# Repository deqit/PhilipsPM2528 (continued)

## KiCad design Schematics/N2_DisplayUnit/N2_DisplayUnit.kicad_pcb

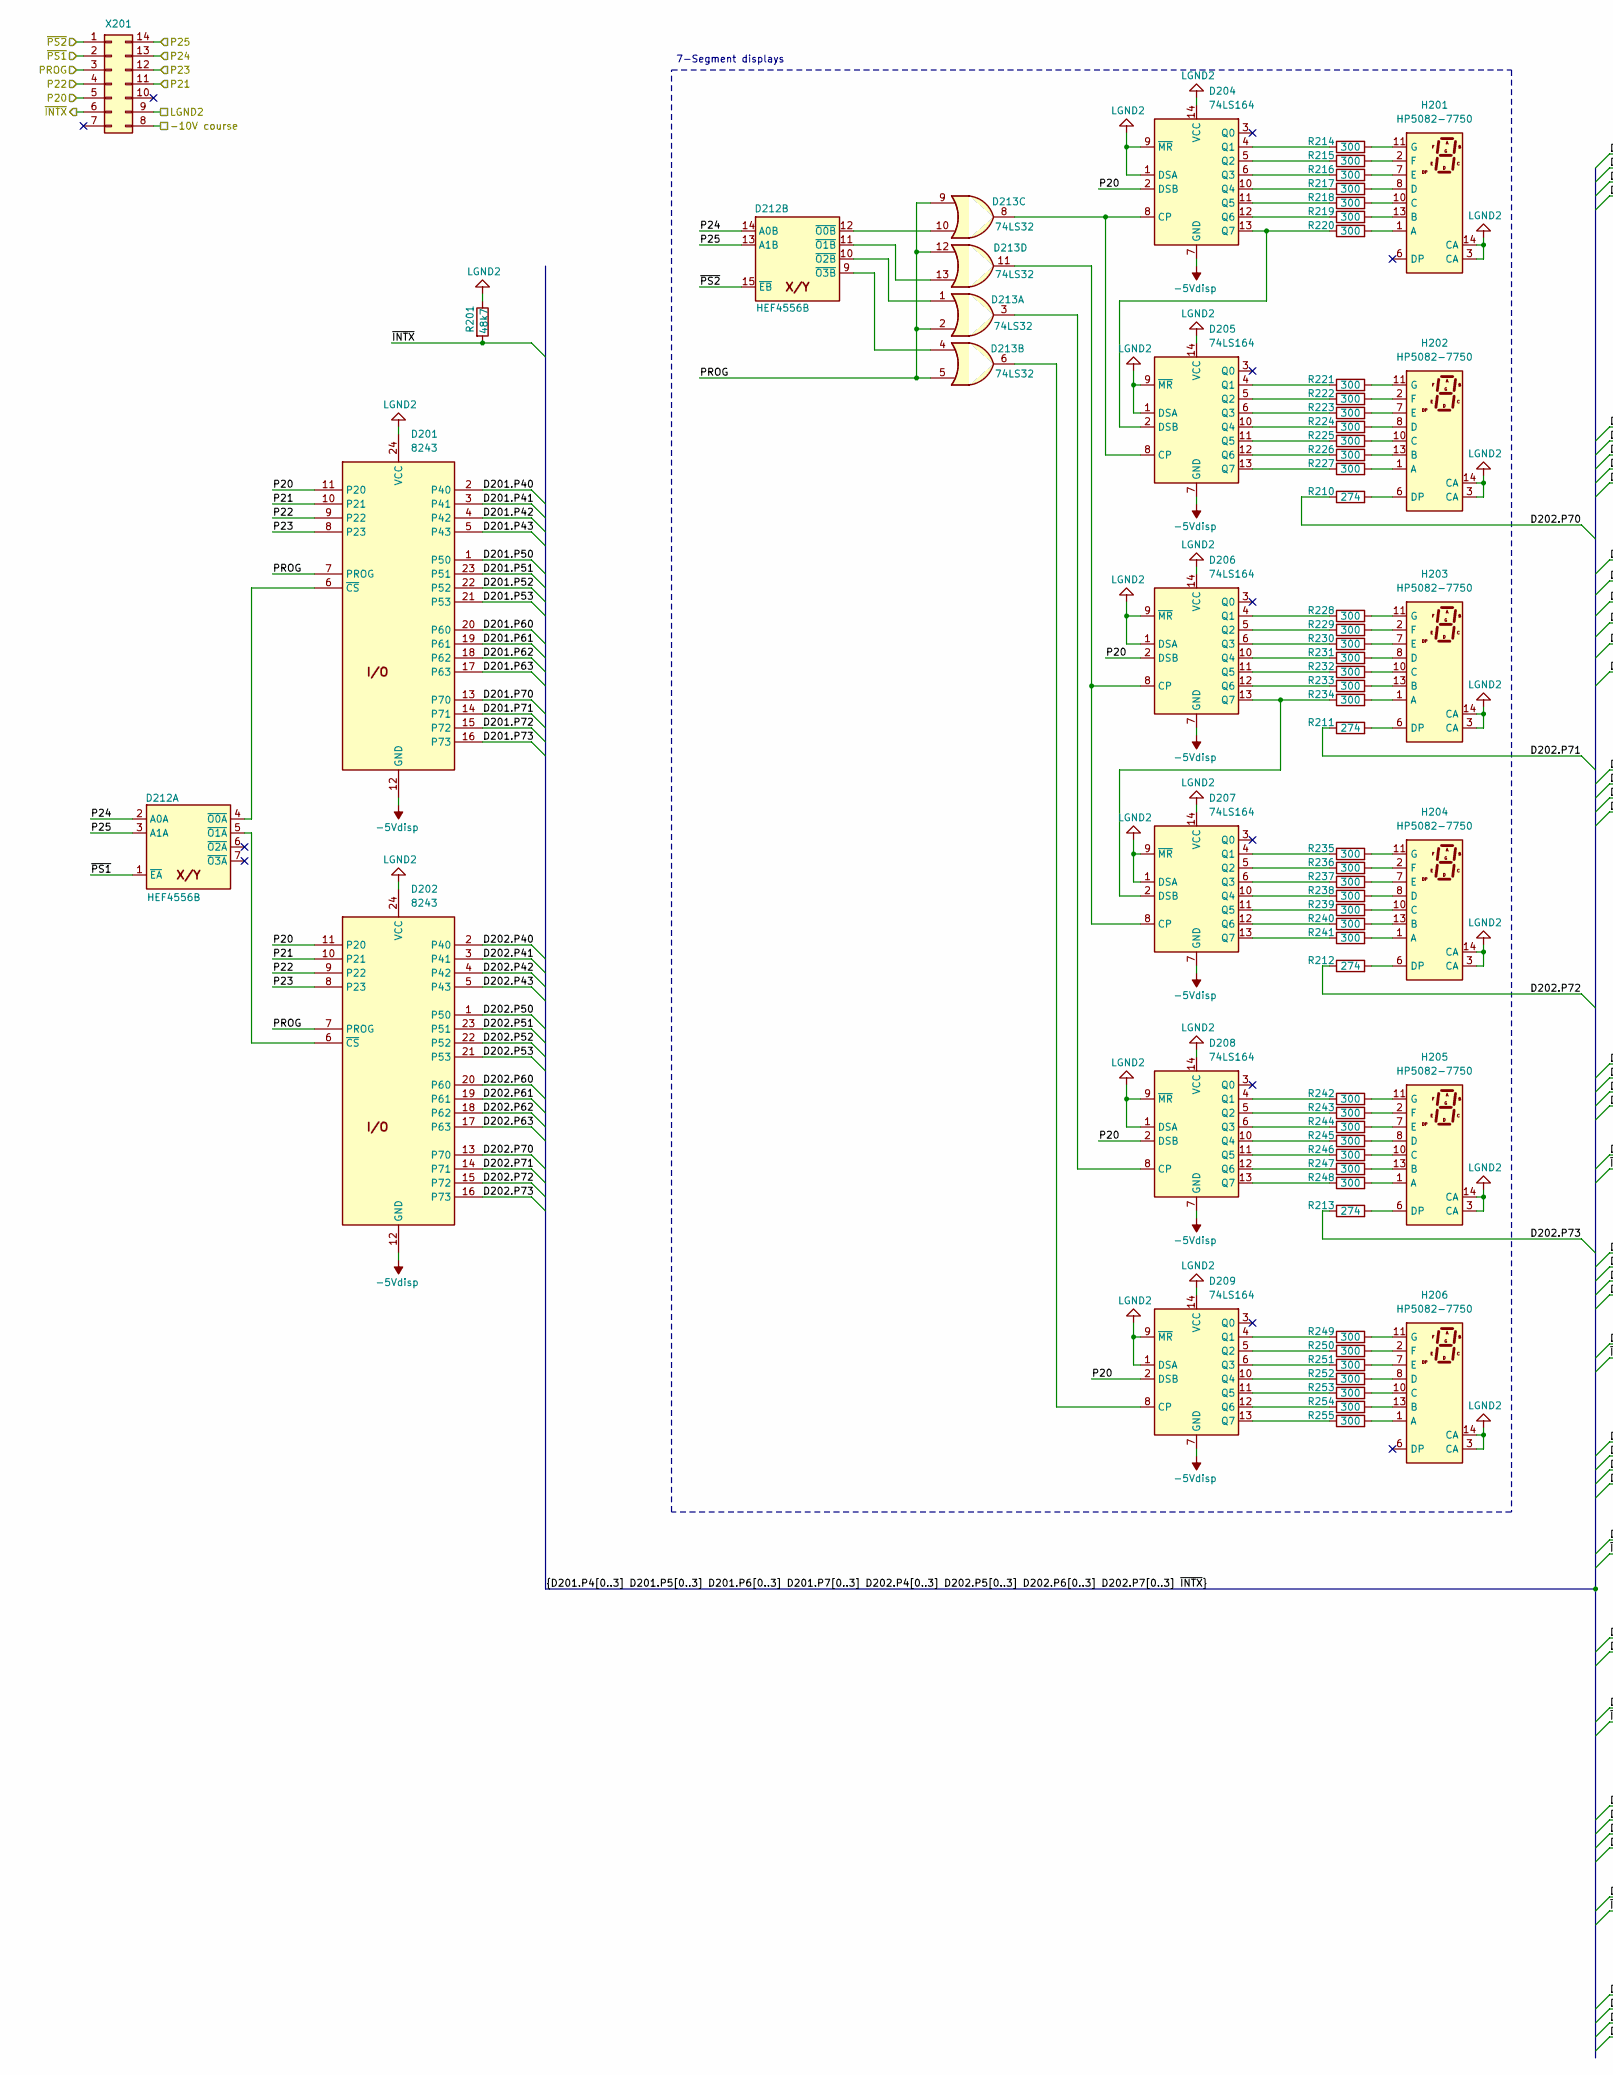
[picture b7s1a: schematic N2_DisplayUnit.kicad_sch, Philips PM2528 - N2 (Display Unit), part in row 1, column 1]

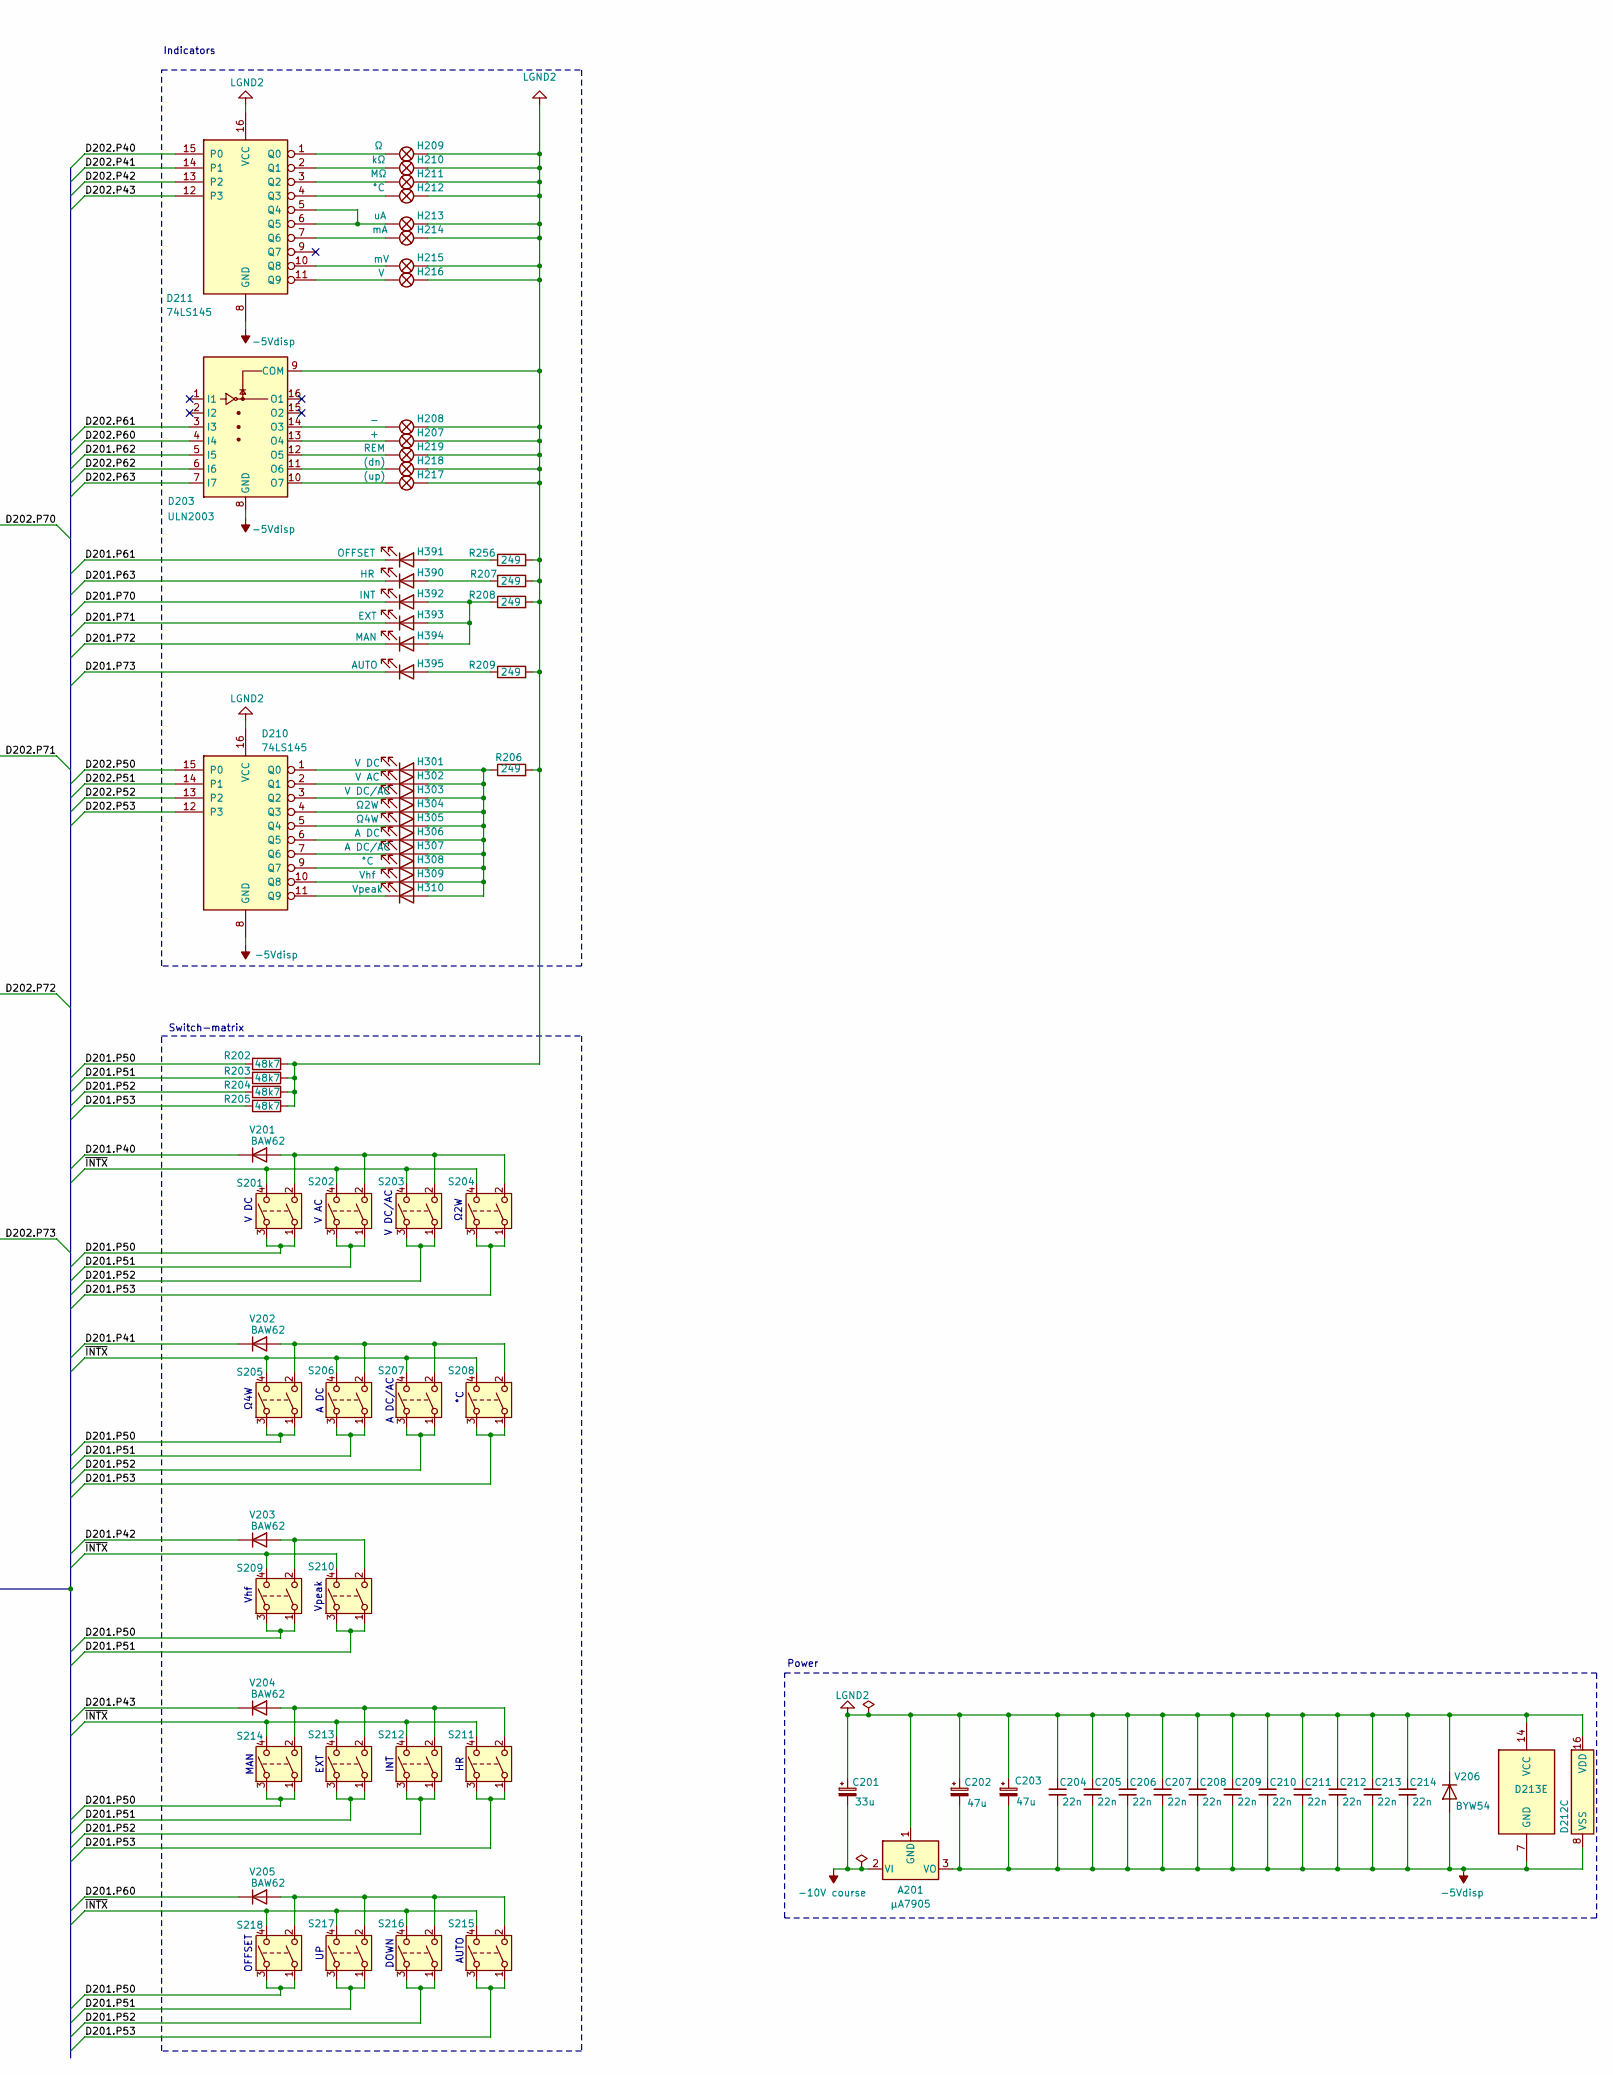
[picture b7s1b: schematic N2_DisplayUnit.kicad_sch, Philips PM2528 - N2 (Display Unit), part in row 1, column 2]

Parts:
A201: µA7905; TO-220-3_Vertical
C201: 33u; CP_Axial_L10.0mm_D4.5mm_P15.00mm_Horizontal
C202, C203: 47u; CP_Axial_L10.0mm_D6.0mm_P15.00mm_Horizontal
C204, C205, C206, C207, C208, C209, C210, C211, C212, C213, C214: 22n; C_Disc_D5.0mm_W2.5mm_P5.00mm
D201, D202: 8243; DIP-24_W15.24mm
D203: ULN2003; DIP-16_W7.62mm
D204, D205, D206, D207, D208, D209: 74LS164; DIP-14_W7.62mm
D210, D211: 74LS145; DIP-16_W7.62mm
D212: HEF4556B; DIP-16_W7.62mm
D213: 74LS32; DIP-14_W7.62mm
H201, H202, H203, H204, H205, H206: HP5082-7750; MAN3820A
H207: +; LED_D3.0mm
H208: -; LED_D3.0mm
H209: Ω; LED_D3.0mm
H210: kΩ; LED_D3.0mm
H211: MΩ; LED_D3.0mm
H212, H308: °C; LED_D3.0mm
H213: uA; LED_D3.0mm
H214: mA; LED_D3.0mm
H215: mV; LED_D3.0mm
H216: V; LED_D3.0mm
H217: (up); LED_D3.0mm
H218: (dn); LED_D3.0mm
H219: REM; LED_D3.0mm
H301: V DC; LED_D3.0mm
H302: V AC; LED_D3.0mm
H303: V DC/AC; LED_D3.0mm
H304: Ω2W; LED_D3.0mm
H305: Ω4W; LED_D3.0mm
H306: A DC; LED_D3.0mm
H307: A DC/AC; LED_D3.0mm
H309: Vhf; LED_D3.0mm
H310: Vpeak; LED_D3.0mm
H390: HR; LED_D3.0mm
H391: OFFSET; LED_D3.0mm
H392: INT; LED_D3.0mm
H393: EXT; LED_D3.0mm
H394: MAN; LED_D3.0mm
H395: AUTO; LED_D3.0mm
R201, R202, R203, R204, R205: 48k7; R_Axial_DIN0207_L6.3mm_D2.5mm_P10.16mm_Horizontal
R206, R207, R208, R209, R256: 249; R_Axial_DIN0207_L6.3mm_D2.5mm_P10.16mm_Horizontal
R210, R211, R212, R213: 274; R_Axial_DIN0207_L6.3mm_D2.5mm_P10.16mm_Horizontal
R214, R215, R216, R217, R218, R219, R220, R221, R222, R223, R224, R225, R226, R227, R228, R229, R230, R231, R232, R233, R234, R235, R236, R237, R238, R239, R240, R241, R242, R243, R244, R245, R246, R247, R248, R249, R250, R251, R252, R253, R254, R255: 300; R_Axial_DIN0207_L6.3mm_D2.5mm_P2.54mm_Vertical
S201, S202, S203, S204, S205, S206, S207, S208, S209, S210, S211, S212, S213, S214, S215, S216, S217, S218: SW_DPST; SW_Push_2P1T_Toggle_CK_PVA1xxH1xxxxxxV2
V201, V202, V203, V204, V205: BAW62; D_DO-35_SOD27_P10.16mm_Horizontal
V206: BYW54; D_DO-35_SOD27_P10.16mm_Horizontal
X201: Conn_02x07_Counter_Clockwise; DIP-14_W10.16mm

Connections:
-5Vdisp: A201.3 (VO), C202.2, C203.2, C204.2, C205.2, C206.2, C207.2, C208.2, C209.2, C210.2, C211.2, C212.2, C213.2, C214.2, D201.12 (GND), D202.12 (GND), D203.8 (GND), D204.7 (GND), D205.7 (GND), D206.7 (GND), D207.7 (GND), D208.7 (GND), D209.7 (GND), D210.8 (GND), D211.8 (GND), D212.8 (VSS), D213.7 (GND), V206.2 (A)
-10V course: A201.2 (VI), C201.2, X201.8
/D201.P40: D201.2 (P40), V201.1 (K)
/D201.P41: D201.3 (P41), V202.1 (K)
/D201.P42: D201.4 (P42), V203.1 (K)
/D201.P43: D201.5 (P43), V204.1 (K)
/D201.P50: D201.1 (P50), R202.2, S201.1, S201.3, S205.1, S205.3, S209.1, S209.3, S214.1, S214.3, S218.1, S218.3
/D201.P51: D201.23 (P51), R203.2, S202.1, S202.3, S206.1, S206.3, S210.1, S210.3, S213.1, S213.3, S217.1, S217.3
/D201.P52: D201.22 (P52), R204.2, S203.1, S203.3, S207.1, S207.3, S212.1, S212.3, S216.1, S216.3
/D201.P53: D201.21 (P53), R205.2, S204.1, S204.3, S208.1, S208.3, S211.1, S211.3, S215.1, S215.3
/D201.P60: D201.20 (P60), V205.1 (K)
/D201.P61: D201.19 (P61), H391.1 (K)
/D201.P62: D201.18 (P62), D203.5 (I5)
/D201.P63: D201.17 (P63), H390.1 (K)
/D201.P70: D201.13 (P70), H392.1 (K)
/D201.P71: D201.14 (P71), H393.1 (K)
/D201.P72: D201.15 (P72), H394.1 (K)
/D201.P73: D201.16 (P73), H395.1 (K)
/D202.P40: D202.2 (P40), D211.15 (P0)
/D202.P41: D202.3 (P41), D211.14 (P1)
/D202.P42: D202.4 (P42), D211.13 (P2)
/D202.P43: D202.5 (P43), D211.12 (P3)
/D202.P50: D202.1 (P50), D210.15 (P0)
/D202.P51: D202.23 (P51), D210.14 (P1)
/D202.P52: D202.22 (P52), D210.13 (P2)
/D202.P53: D202.21 (P53), D210.12 (P3)
/D202.P60: D202.20 (P60), D203.4 (I4)
/D202.P61: D202.19 (P61), D203.3 (I3)
/D202.P62: D202.18 (P62), D203.6 (I6)
/D202.P63: D202.17 (P63), D203.7 (I7)
/D202.P70: D202.13 (P70), R210.1
/D202.P71: D202.14 (P71), R211.1
/D202.P72: D202.15 (P72), R212.1
/D202.P73: D202.16 (P73), R213.1
/LGND2: A201.1 (GND), C201.1, C202.1, C203.1, C204.1, C205.1, C206.1, C207.1, C208.1, C209.1, C210.1, C211.1, C212.1, C213.1, C214.1, D201.24 (VCC), D202.24 (VCC), D203.9 (COM), D204.1 (DSA), D204.9 (~MR), D204.14 (VCC), D205.1 (DSA), D205.9 (~MR), D205.14 (VCC), D206.1 (DSA), D206.9 (~MR), D206.14 (VCC), D207.1 (DSA), D207.9 (~MR), D207.14 (VCC), D208.1 (DSA), D208.9 (~MR), D208.14 (VCC), D209.1 (DSA), D209.9 (~MR), D209.14 (VCC), D210.16 (VCC), D211.16 (VCC), D212.16 (VDD), D213.14 (VCC), H201.3 (CA), H201.14 (CA), H202.3 (CA), H202.14 (CA), H203.3 (CA), H203.14 (CA), H204.3 (CA), H204.14 (CA), H205.3 (CA), H205.14 (CA), H206.3 (CA), H206.14 (CA), H207.2, H208.2, H209.2, H210.2, H211.2, H212.2, H213.2, H214.2, H215.2, H216.2, H217.2, H218.2, H219.2, R201.1, R202.1, R203.1, R204.1, R205.1, R206.2, R207.2, R208.2, R209.2, R256.2, V206.1 (K), X201.9
/P20: D201.11 (P20), D202.11 (P20), D204.2 (DSB), D206.2 (DSB), D208.2 (DSB), D209.2 (DSB), X201.5
/P21: D201.10 (P21), D202.10 (P21), X201.11
/P22: D201.9 (P22), D202.9 (P22), X201.4
/P23: D201.8 (P23), D202.8 (P23), X201.12
/P24: D212.2 (A0A), D212.14 (A0B), X201.13
/P25: D212.3 (A1A), D212.13 (A1B), X201.14
/PROG: D201.7 (PROG), D202.7 (PROG), D213.2, D213.5, D213.9, D213.12, X201.3
/~INTX: R201.2, S201.4, S202.4, S203.4, S204.4, S205.4, S206.4, S207.4, S208.4, S209.4, S210.4, S211.4, S212.4, S213.4, S214.4, S215.4, S216.4, S217.4, S218.4, X201.6
/~PS1: D212.1 (~EA), X201.2
/~PS2: D212.15 (~EB), X201.1
unnamed: D201.6 (~CS), D212.4 (~O0A)
unnamed: D202.6 (~CS), D212.5 (~O1A)
unnamed: D203.14 (O3), H208.1
unnamed: D203.13 (O4), H207.1
unnamed: D203.12 (O5), H219.1
unnamed: D203.11 (O6), H218.1
unnamed: D203.10 (O7), H217.1
unnamed: D204.8 (CP), D205.8 (CP), D213.8
unnamed: D204.4 (Q1), R214.1
unnamed: D204.5 (Q2), R215.1
unnamed: D204.6 (Q3), R216.1
unnamed: D204.10 (Q4), R217.1
unnamed: D204.11 (Q5), R218.1
unnamed: D204.12 (Q6), R219.1
unnamed: D204.13 (Q7), D205.2 (DSB), R220.1
unnamed: D205.4 (Q1), R221.1
unnamed: D205.5 (Q2), R222.1
unnamed: D205.6 (Q3), R223.1
unnamed: D205.10 (Q4), R224.1
unnamed: D205.11 (Q5), R225.1
unnamed: D205.12 (Q6), R226.1
unnamed: D205.13 (Q7), R227.1
unnamed: D206.8 (CP), D207.8 (CP), D213.11
unnamed: D206.4 (Q1), R228.1
unnamed: D206.5 (Q2), R229.1
unnamed: D206.6 (Q3), R230.1
unnamed: D206.10 (Q4), R231.1
unnamed: D206.11 (Q5), R232.1
unnamed: D206.12 (Q6), R233.1
unnamed: D206.13 (Q7), D207.2 (DSB), R234.1
unnamed: D207.4 (Q1), R235.1
unnamed: D207.5 (Q2), R236.1
unnamed: D207.6 (Q3), R237.1
unnamed: D207.10 (Q4), R238.1
unnamed: D207.11 (Q5), R239.1
unnamed: D207.12 (Q6), R240.1
unnamed: D207.13 (Q7), R241.1
unnamed: D208.8 (CP), D213.3
unnamed: D208.4 (Q1), R242.1
unnamed: D208.5 (Q2), R243.1
unnamed: D208.6 (Q3), R244.1
unnamed: D208.10 (Q4), R245.1
unnamed: D208.11 (Q5), R246.1
unnamed: D208.12 (Q6), R247.1
unnamed: D208.13 (Q7), R248.1
unnamed: D209.8 (CP), D213.6
unnamed: D209.4 (Q1), R249.1
unnamed: D209.5 (Q2), R250.1
unnamed: D209.6 (Q3), R251.1
unnamed: D209.10 (Q4), R252.1
unnamed: D209.11 (Q5), R253.1
unnamed: D209.12 (Q6), R254.1
unnamed: D209.13 (Q7), R255.1
unnamed: D210.1 (Q0), H301.1 (K)
unnamed: D210.2 (Q1), H302.1 (K)
unnamed: D210.3 (Q2), H303.1 (K)
unnamed: D210.4 (Q3), H304.1 (K)
unnamed: D210.5 (Q4), H305.1 (K)
unnamed: D210.6 (Q5), H306.1 (K)
unnamed: D210.7 (Q6), H307.1 (K)
unnamed: D210.9 (Q7), H308.1 (K)
unnamed: D210.10 (Q8), H309.1 (K)
unnamed: D210.11 (Q9), H310.1 (K)
unnamed: D211.1 (Q0), H209.1
unnamed: D211.2 (Q1), H210.1
unnamed: D211.3 (Q2), H211.1
unnamed: D211.4 (Q3), H212.1
unnamed: D211.5 (Q4), D211.6 (Q5), H213.1
unnamed: D211.7 (Q6), H214.1
unnamed: D211.10 (Q8), H215.1
unnamed: D211.11 (Q9), H216.1
unnamed: D212.12 (~O0B), D213.10
unnamed: D212.11 (~O1B), D213.13
unnamed: D212.10 (~O2B), D213.1
unnamed: D212.9 (~O3B), D213.4
unnamed: H201.1 (A), R220.2
unnamed: H201.13 (B), R219.2
unnamed: H201.10 (C), R218.2
unnamed: H201.8 (D), R217.2
unnamed: H201.7 (E), R216.2
unnamed: H201.2 (F), R215.2
unnamed: H201.11 (G), R214.2
unnamed: H202.1 (A), R227.2
unnamed: H202.13 (B), R226.2
unnamed: H202.10 (C), R225.2
unnamed: H202.8 (D), R224.2
unnamed: H202.6 (DP), R210.2
unnamed: H202.7 (E), R223.2
unnamed: H202.2 (F), R222.2
unnamed: H202.11 (G), R221.2
unnamed: H203.1 (A), R234.2
unnamed: H203.13 (B), R233.2
unnamed: H203.10 (C), R232.2
unnamed: H203.8 (D), R231.2
unnamed: H203.6 (DP), R211.2
unnamed: H203.7 (E), R230.2
unnamed: H203.2 (F), R229.2
unnamed: H203.11 (G), R228.2
unnamed: H204.1 (A), R241.2
unnamed: H204.13 (B), R240.2
unnamed: H204.10 (C), R239.2
unnamed: H204.8 (D), R238.2
unnamed: H204.6 (DP), R212.2
unnamed: H204.7 (E), R237.2
unnamed: H204.2 (F), R236.2
unnamed: H204.11 (G), R235.2
unnamed: H205.1 (A), R248.2
unnamed: H205.13 (B), R247.2
unnamed: H205.10 (C), R246.2
unnamed: H205.8 (D), R245.2
unnamed: H205.6 (DP), R213.2
unnamed: H205.7 (E), R244.2
unnamed: H205.2 (F), R243.2
unnamed: H205.11 (G), R242.2
unnamed: H206.1 (A), R255.2
unnamed: H206.13 (B), R254.2
unnamed: H206.10 (C), R253.2
unnamed: H206.8 (D), R252.2
unnamed: H206.7 (E), R251.2
unnamed: H206.2 (F), R250.2
unnamed: H206.11 (G), R249.2
unnamed: H301.2 (A), H302.2 (A), H303.2 (A), H304.2 (A), H305.2 (A), H306.2 (A), H307.2 (A), H308.2 (A), H309.2 (A), H310.2 (A), R206.1
unnamed: H390.2 (A), R207.1
unnamed: H391.2 (A), R256.1
unnamed: H392.2 (A), H393.2 (A), H394.2 (A), R208.1
unnamed: H395.2 (A), R209.1
unnamed: S201.2, S202.2, S203.2, S204.2, V201.2 (A)
unnamed: S205.2, S206.2, S207.2, S208.2, V202.2 (A)
unnamed: S209.2, S210.2, V203.2 (A)
unnamed: S211.2, S212.2, S213.2, S214.2, V204.2 (A)
unnamed: S215.2, S216.2, S217.2, S218.2, V205.2 (A)

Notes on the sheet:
Vhf
AUTO
Power
OFFSET
MAN
DOWN
V AC
Indicators
V DC
Switch-matrix
A DC
V DC/AC
Vpeak
EXT
7-Segment displays
Ω4W
Ω2W
A DC/AC
INT

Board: 2 copper layers, 144 parts (0 on the bottom side), 176 nets, no tracks yet.

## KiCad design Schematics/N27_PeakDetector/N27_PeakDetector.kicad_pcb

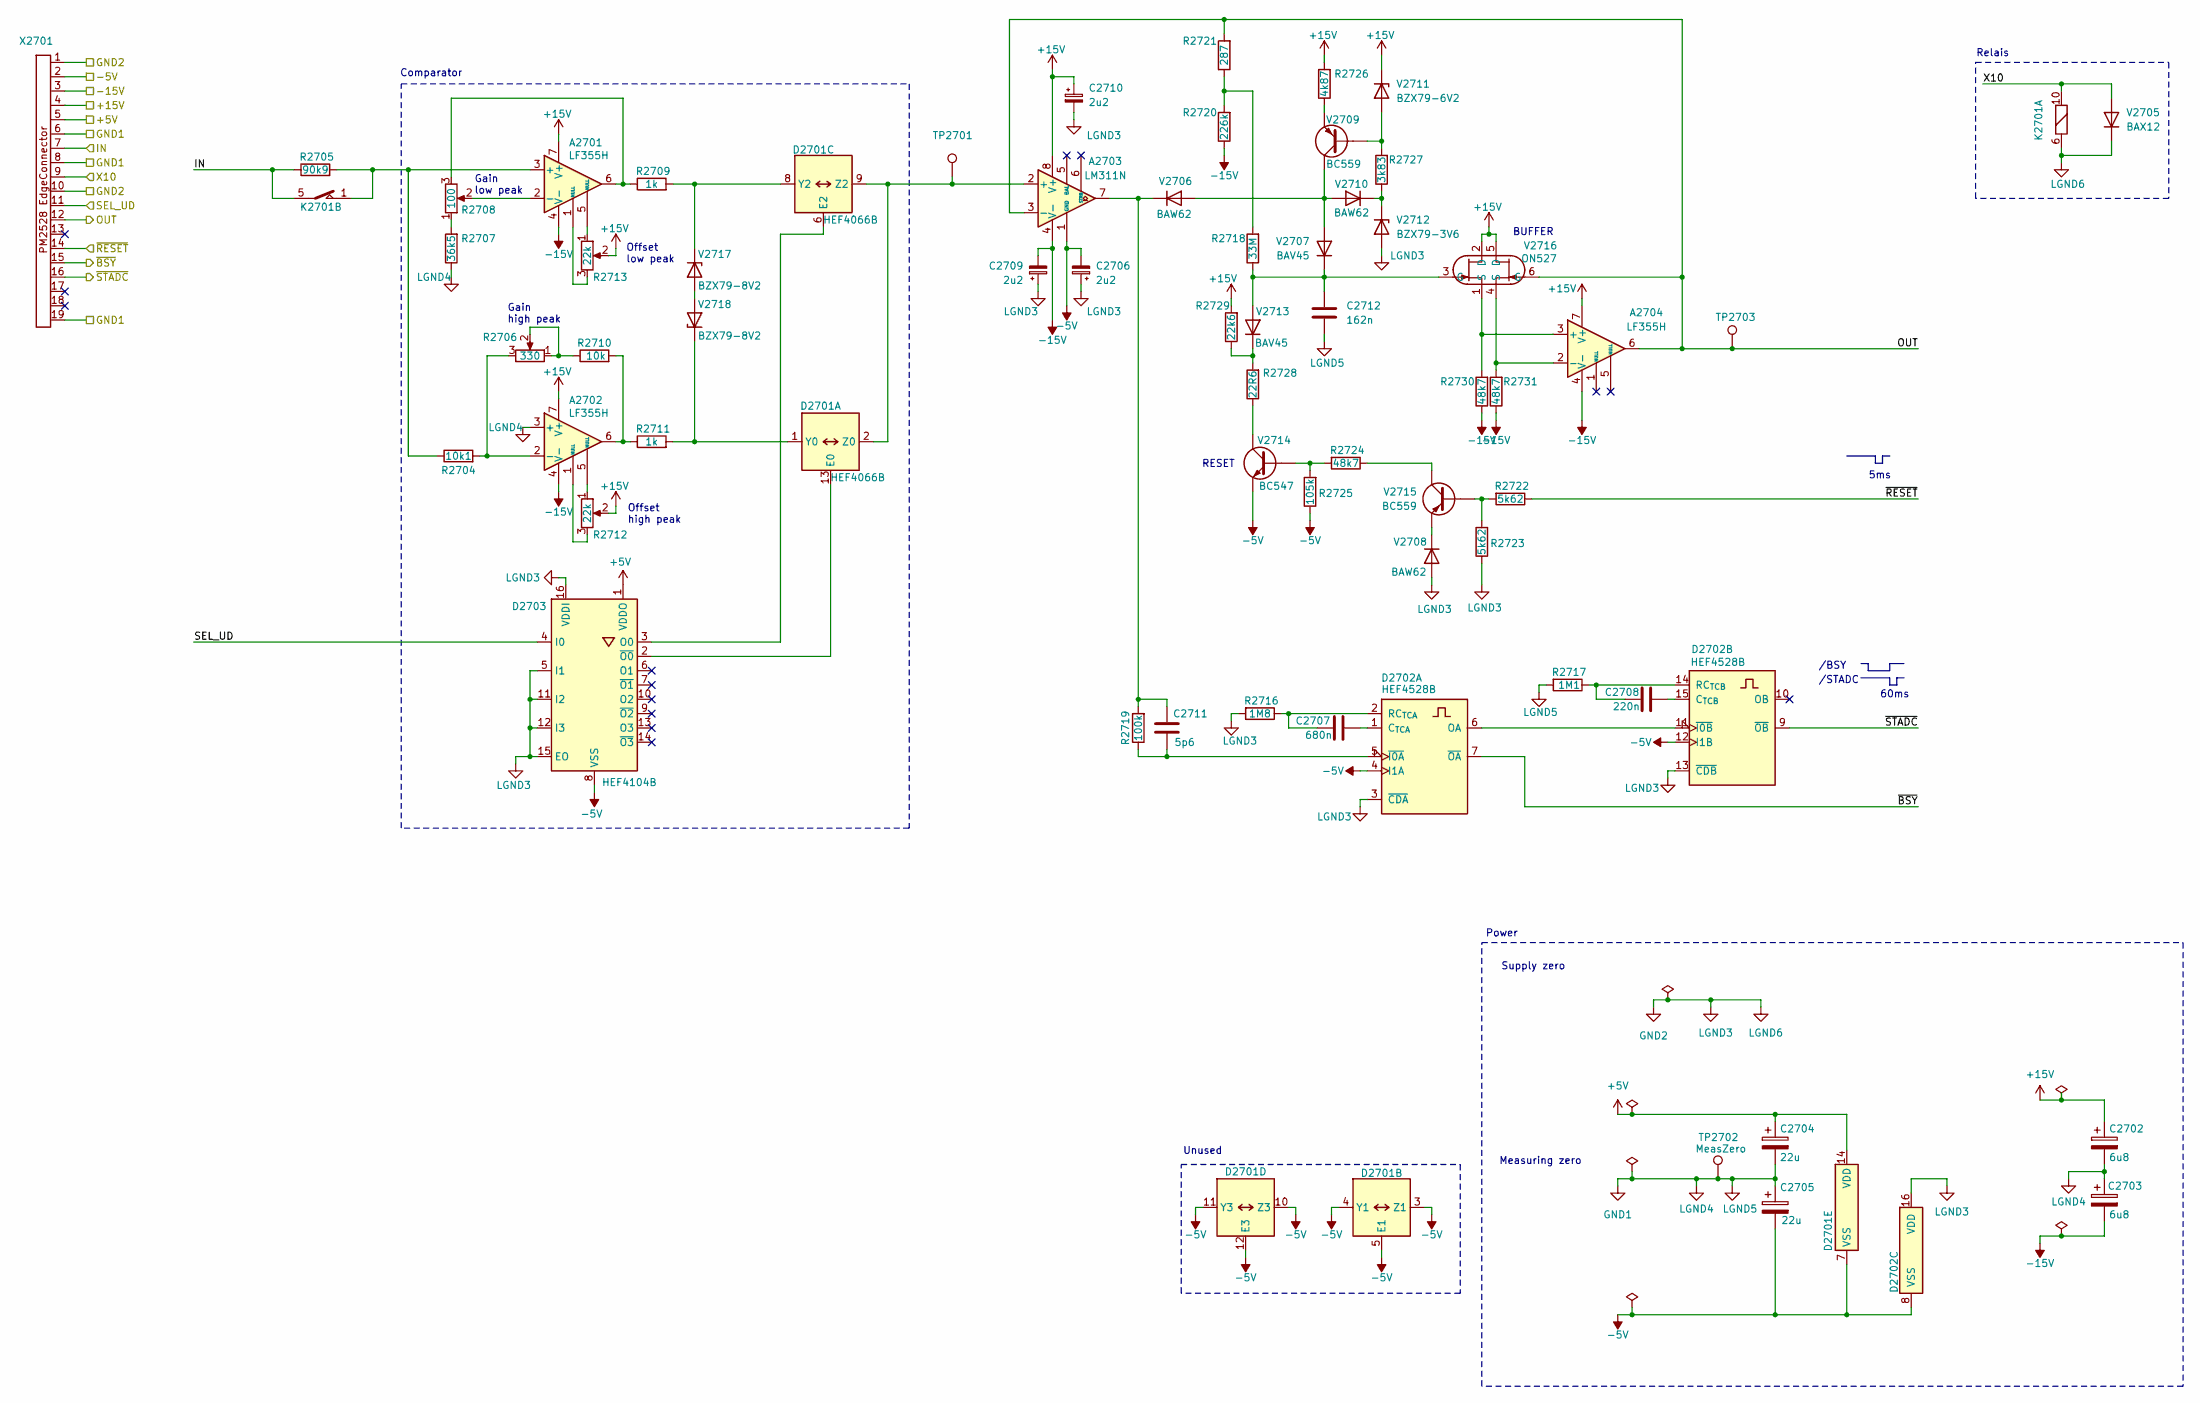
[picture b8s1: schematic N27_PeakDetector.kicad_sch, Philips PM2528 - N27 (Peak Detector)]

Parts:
A2701, A2702, A2704: LF355H; DIP-8_W7.62mm
A2703: LM311N; DIP-8_W7.62mm
C2702, C2703: 6u8; CP_Radial_Tantal_D4.5mm_P5.00mm
C2704, C2705: 22u; CP_Radial_Tantal_D4.5mm_P5.00mm
C2706, C2709, C2710: 2u2; C_Disc_D5.0mm_W2.5mm_P5.00mm
C2707: 680n; C_Rect_L18.0mm_W5.0mm_P15.00mm_FKS3_FKP3
C2708: 220n; C_Rect_L13.0mm_W4.0mm_P10.00mm_FKS3_FKP3_MKS4
C2711: 5p6
C2712: 162n; CP_Axial_L25.0mm_D10.0mm_P30.00mm_Horizontal
D2701: HEF4066B; DIP-14_W7.62mm
D2702: HEF4528B; DIP-16_W7.62mm
D2703: HEF4104B; DIP-16_W7.62mm
K2701: (no value)
R2704: 10k1; R_Axial_DIN0207_L6.3mm_D2.5mm_P10.16mm_Horizontal
R2705: 90k9; R_Axial_DIN0207_L6.3mm_D2.5mm_P10.16mm_Horizontal
R2706: 330; Trimmer vertical
R2707: 36k5; R_Axial_DIN0207_L6.3mm_D2.5mm_P10.16mm_Horizontal
R2708: 100; Trimmer vertical
R2709, R2711: 1k; R_Axial_DIN0207_L6.3mm_D2.5mm_P10.16mm_Horizontal
R2710: 10k; R_Axial_DIN0207_L6.3mm_D2.5mm_P10.16mm_Horizontal
R2712, R2713: 22k; Trimmer vertical
R2716: 1M8; R_Axial_DIN0207_L6.3mm_D2.5mm_P10.16mm_Horizontal
R2717: 1M1; R_Axial_DIN0207_L6.3mm_D2.5mm_P10.16mm_Horizontal
R2718: 33M; R_Axial_DIN0309_L9.0mm_D3.2mm_P15.24mm_Horizontal
R2719: 100k; R_Axial_DIN0207_L6.3mm_D2.5mm_P10.16mm_Horizontal
R2720: 226k; R_Axial_DIN0207_L6.3mm_D2.5mm_P10.16mm_Horizontal
R2721: 287; R_Axial_DIN0207_L6.3mm_D2.5mm_P10.16mm_Horizontal
R2722, R2723: 5k62; R_Axial_DIN0207_L6.3mm_D2.5mm_P10.16mm_Horizontal
R2724, R2730, R2731: 48k7; R_Axial_DIN0207_L6.3mm_D2.5mm_P10.16mm_Horizontal
R2725: 105k; R_Axial_DIN0207_L6.3mm_D2.5mm_P10.16mm_Horizontal
R2726: 4k87; R_Axial_DIN0207_L6.3mm_D2.5mm_P10.16mm_Horizontal
R2727: 3k83; R_Axial_DIN0207_L6.3mm_D2.5mm_P10.16mm_Horizontal
R2728: 22R6; R_Axial_DIN0207_L6.3mm_D2.5mm_P10.16mm_Horizontal
R2729: 22k6; R_Axial_DIN0207_L6.3mm_D2.5mm_P10.16mm_Horizontal
TP2701, TP2703: Pin_D0.9mm_L10.0mm_W2.4mm_FlatFork
TP2702: MeasZero; Pin_D0.9mm_L10.0mm_W2.4mm_FlatFork
V2705: BAX12; D_DO-34_SOD68_P10.16mm_Horizontal
V2706, V2708, V2710: BAW62; D_DO-35_SOD27_P10.16mm_Horizontal
V2707, V2713: BAV45; BAV45_TO-18-2
V2709, V2715: BC559; TO-92_Inline
V2711: BZX79-6V2; D_DO-34_SOD68_P10.16mm_Horizontal
V2712: BZX79-3V6; D_DO-35_SOD27_P10.16mm_Horizontal
V2714: BC547; TO-92_Inline
V2716: ON527; TO-75-6
V2717, V2718: BZX79-8V2; D_DO-35_SOD27_P10.16mm_Horizontal
X2701: PM2528Edgeconnector

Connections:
+5V: C2704.1, D2701.14 (VDD), D2703.1 (VDDO), X2701.5
+15V: A2701.7 (V+), A2702.7 (V+), A2703.8 (V+), A2704.7 (V+), C2702.1, C2710.1, R2712.2, R2713.2, R2726.2, R2729.2, V2711.1 (K), V2716.2 (D), V2716.5 (D), X2701.4
-5V: A2703.1 (GND), C2705.2, C2706.2, D2701.3 (Z1), D2701.4 (Y1), D2701.5 (E1), D2701.7 (VSS), D2701.10 (Z3), D2701.11 (Y3), D2701.12 (E3), D2702.4 (I1A), D2702.8 (VSS), D2702.12 (I1B), D2703.8 (VSS), R2725.1, V2714.3 (E), X2701.2
-15V: A2701.4 (V-), A2702.4 (V-), A2703.4 (V-), A2704.4 (V-), C2703.2, C2709.2, R2720.1, R2730.1, R2731.1, X2701.3
/IN: K2701.5, R2705.1, X2701.7
/OUT: A2703.3 (-), A2704.6, R2721.2, TP2703.1 (1_1), V2716.6 (G), X2701.12
/SEL_UD: D2703.4 (I0), X2701.11
/X10: K2701.10, V2705.2 (A), X2701.9
/~BSY: D2702.7 (~OA), X2701.15
/~RESET: R2722.1, X2701.14
/~STADC: D2702.9 (~OB), X2701.16
GND1: A2702.3 (+), C2702.2, C2703.1, C2704.2, C2705.1, C2712.2, R2707.1, R2717.2, TP2702.1 (1_1), X2701.6, X2701.8, X2701.19
GND2: C2706.1, C2709.1, C2710.2, D2702.3 (~CDA), D2702.13 (~CDB), D2702.16 (VDD), D2703.5 (I1), D2703.11 (I2), D2703.12 (I3), D2703.15 (EO), D2703.16 (VDDI), K2701.6, R2716.2, R2723.1, V2705.1 (K), V2708.2 (A), V2712.2 (A), X2701.1, X2701.10
unnamed: A2701.3 (+), K2701.1, R2704.1, R2705.2
unnamed: A2701.2 (-), R2708.2
unnamed: A2701.1 (NULL), R2713.3
unnamed: A2701.5 (NULL), R2713.1
unnamed: A2701.6, R2708.3, R2709.1
unnamed: A2702.2 (-), R2704.2, R2706.3
unnamed: A2702.1 (NULL), R2712.3
unnamed: A2702.5 (NULL), R2712.1
unnamed: A2702.6, R2710.2, R2711.1
unnamed: A2703.2 (+), D2701.2 (Z0), D2701.9 (Z2), TP2701.1 (1_1)
unnamed: A2704.3 (+), R2730.2, V2716.1 (S)
unnamed: A2704.2 (-), R2731.2, V2716.4 (S)
unnamed: D2701.13 (E0), D2703.2 (~O0)
unnamed: D2701.1 (Y0), R2711.2, V2718.1 (K)
unnamed: D2701.6 (E2), D2703.3 (O0)
unnamed: D2701.8 (Y2), R2709.2, V2717.1 (K)
unnamed: C2707.2, D2702.1 (C_{TCA})
unnamed: D2702.6 (OA), D2702.11 (~I0B)
unnamed: C2707.1, D2702.2 (RC_{TCA}), R2716.1
unnamed: C2711.2, D2702.5 (~I0A), R2719.1
unnamed: C2708.2, D2702.15 (C_{TCB})
unnamed: C2708.1, D2702.14 (RC_{TCB}), R2717.1
unnamed: R2706.1, R2706.2, R2710.1
unnamed: R2707.2, R2708.1
unnamed: R2718.2, R2720.2, R2721.1
unnamed: V2706.2 (A), V2707.2 (A), V2709.1 (C), V2710.2 (A)
unnamed: A2703.7, C2711.1, R2719.2, V2706.1 (K)
unnamed: C2712.1, R2718.1, V2707.1 (K), V2713.2 (A), V2716.3 (G)
unnamed: V2708.1 (K), V2715.3 (E)
unnamed: R2727.2, V2709.2 (B), V2711.2 (A)
unnamed: R2726.1, V2709.3 (E)
unnamed: R2727.1, V2710.1 (K), V2712.1 (K)
unnamed: R2728.2, R2729.1, V2713.1 (K)
unnamed: R2724.2, R2725.2, V2714.2 (B)
unnamed: R2728.1, V2714.1 (C)
unnamed: R2722.2, R2723.2, V2715.2 (B)
unnamed: R2724.1, V2715.1 (C)
unnamed: V2717.2 (A), V2718.2 (A)

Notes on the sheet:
Gain high peak
Relais
Offset high peak
Gain low peak
Power
Supply zero
BUFFER
RESET
5ms
/BSY
Measuring zero
Comparator
Unused
60ms
/STADC
Offset low peak

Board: 2 copper layers, 62 parts (0 on the bottom side), 51 nets, no tracks yet.

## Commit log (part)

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2024-08-15 Added README.md
2024-08-15 First version
2024-08-15 Added gitignore
2024-08-15 Deleted PM2528Riser-backups
2024-08-29 Version 2
2024-08-29 Remove backups
2024-08-29 Removed backups
2024-08-29 Added new files for N21
2024-08-29 Remove cache-files
2024-08-29 Deleted fp-info-cache
2024-08-29 Expanded .gitignore
2024-10-04 Replaced testpins with testloops/beads
2024-11-01 Added N22/N23
2024-11-01 Reformat folders
2025-04-08 Updates, add N25
2025-04-27 Updated info, updated N22
2025-05-25 Started with N24
2025-05-29 Small updates, N25 also
2025-05-30 N25 RMS Ok!
2025-05-30 Updated relais-xreference
2025-07-06 Update schematics, move projectlibraries to D:
2025-07-24 Restructure folders, added EPROM-dumps
2025-07-28 Restructure folders, added EPROMs and Ghidra-project
2025-08-05 Lotsofchanges. Included Ghidra-project and correct firmware-images
2025-08-08 Reworked N20/N21
2025-08-08 Added readme.
2025-08-08 Added Ghidra-stuff
2025-08-08 Restructure folders
2025-08-08 Remove obsolete files
2025-08-10 Small modifications, more disassembly
2025-08-10 Reorganize Ghidra folderstructure Add some comments in assembly
2025-08-15 Updated N24 schema/PCB
2025-08-17 Updated some component-values
2025-08-17 Added N30 schema/PCB Small additions to disassembly
2025-08-23 Updated disassembly some more Moved PM2528 footprints/3D to subfolder
2025-08-31 More disassembly More info in Info-Excel-sheet
2025-09-10 Some more disassembly
2025-09-12 Some more disassembly, optimize N20 schematics (naming of signals)
2025-09-13 Lotsadisassembly
2025-09-21 Small updates Some GPIB-analyzing-functions found.
2025-10-05 Added a simple POC-ROM (counting from 9 to 1)
2025-10-10 Lotsofassembly-comments Added extra MCS48-info Updated Excelsheet
2025-10-17 Added LA-traces, some assembly-comments
2025-10-19 Add link to hackaday.io
2025-11-02 Added ADC controlflow (Archimate)
2025-11-02 Deepdive ADC (wip)
2025-11-15 Added ADC-deepdive txts
2025-11-15 Deepdive - added more text/images
2025-11-18 Created new screenshots, removed todo-part of the text. Still todo.
2025-11-18 Removed one paragraph
2025-11-19 Removed Temp-files
2025-11-19 Added N20 deepdive
2025-11-29 Small textual changes
2025-11-29 Added N21 deepdive
2025-11-29 General info added
2025-11-29 Fixed type
2025-11-29 Small things
2025-11-30 Included signal-names
2025-11-30 Filerename-typo
2025-11-30 Included schematics
2025-12-03 Added PCB
2025-12-03 Rename ADC Core to ADC Analog
2025-12-03 Textual changes
2025-12-03 Included PCBs, Risercard and 3D-views
2025-12-03 PCBs in color
2025-12-16 Schematic-analyses N20
2025-12-16 tempfiles
2025-12-21 More N20
2026-01-13 name of section
2026-01-16 More N20, update Ghidra-project to most recent Ghidra version
